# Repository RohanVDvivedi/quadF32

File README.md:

# Flight controller using STM32F103
[Documentation and demonstration video link](https://youtu.be/UyUF_jVTML4)

### setup requirements
(for programming stm32f103 microcontroller)

* Linux debian (to use make build system and code upload tool stm32flash)
* sublime/vi/vim/gedit any texteditor
* ARM cross compiler toolchain
  * sudo apt-get install gcc-arm-none-eabi binutils-arm-none-eabi
* stm32flash to flash the controller, assuming the controller has default factory bootloader
  * sudo apt-get install stm32flash
* stm32f103 microcontroller, with default factory bootloader (must)
* usb to uart converter
  * PL2303HX, CP2102, ftdi etc

### sensors
 * mpu6050  sccelerometer and gyroscope
 * hmc5883l magnetometer
 * ms5611 barometer

### additional accessories
 * rc transmitter and receiver

#### [STM32F10x Reference Manual](https://www.st.com/resource/en/reference_manual/cd00171190-stm32f101xx-stm32f102xx-stm32f103xx-stm32f105xx-and-stm32f107xx-advanced-arm-based-32-bit-mcus-stmicroelectronics.pdf)

### connections (from microcontroller)
 * I2c1 {PB6, PB7} -> GY86 sensor {SCL, SDA}
 * UART1 {PA10, PA9} -> UART debug port {RX, TX}
 * {PB10, PB11, PB12, PB13, PB14, PB15} -> RC receiver
 * {PA0, PA1, PA2, PA3} -> PWM to ESCs of corresponding motors (Left Front, Right Front, Left Back, Right Back) of Quadcopter
 
### PCB designs
 * You will find the .sch and .brd, QuadF32 flight controller board designs in the Eagle_CAD folder.
 * It would also include a generated .cam file that I used for building my board, I would request you to use a different cam file provided by your pcb manufacturer.
 * The folder also does include .lbr library for the stm32f103 module, that I am using.

### Third party acknowledgements
 * [STM32F103-c8t6 eagle cad library](https://os.mbed.com/users/hudakz/code/STM32F103C8T6_Hello/file/accb2c83a007/mbed-STM32F103C8T6.lib/)

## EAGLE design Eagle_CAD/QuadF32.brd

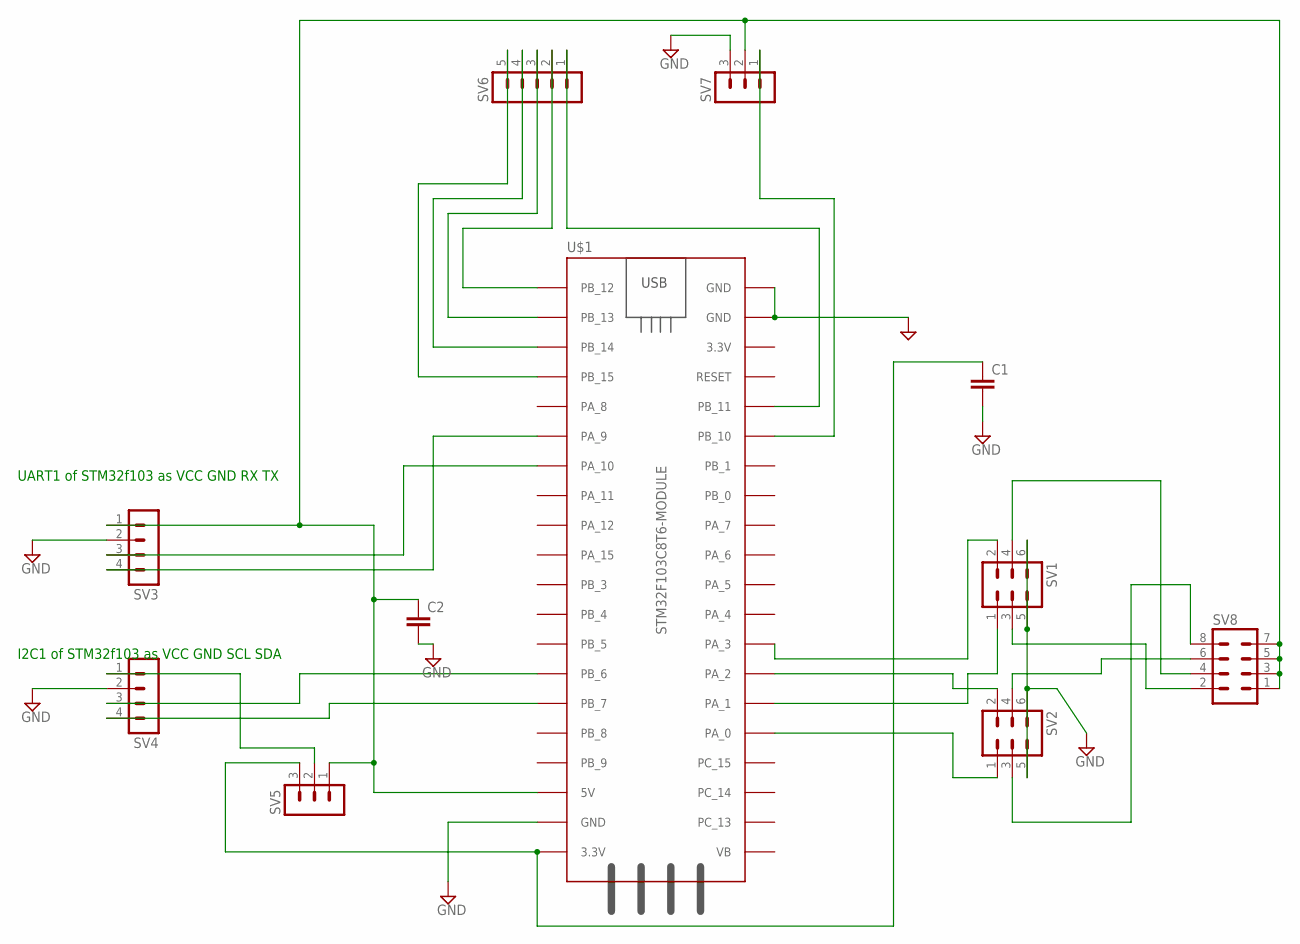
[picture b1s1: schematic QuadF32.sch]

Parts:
C1, C2: C5/2.5; C5B2.5
SV1, SV2: MA03-2
SV3, SV4: MA04-1
SV5, SV7: MA03-1
SV6: MA05-1
SV8: MA04-2
U$1: STM32F103C8T6-MODULE

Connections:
GND: C1.2, C2.2, SV1.5, SV1.6, SV2.5, SV2.6, SV3.2, SV4.2, SV7.3, U$1.GND_1 (GND), U$1.GND_2 (GND), U$1.GND_3 (GND)
unnamed: SV4.3, U$1.PB_6
unnamed: SV4.4, U$1.PB_7
unnamed: SV3.3, U$1.PA_10
unnamed: SV3.4, U$1.PA_9
unnamed: SV2.1, U$1.PA_0
unnamed: SV2.2, U$1.PA_2
unnamed: SV1.1, U$1.PA_1
unnamed: SV1.2, U$1.PA_3
unnamed: SV6.5, U$1.PB_15
unnamed: SV6.4, U$1.PB_14
unnamed: SV6.3, U$1.PB_13
unnamed: SV6.2, U$1.PB_12
unnamed: SV6.1, U$1.PB_11
unnamed: SV7.1, U$1.PB_10
unnamed: SV1.4, SV8.4
unnamed: C1.1, SV5.3, U$1.3.3V_1 (3.3V)
unnamed: SV4.1, SV5.2
unnamed: C2.1, SV3.1, SV5.1, SV7.2, SV8.1, SV8.3, SV8.5, SV8.7, U$1.5V
unnamed: SV2.3, SV8.8
unnamed: SV2.4, SV8.6
unnamed: SV1.3, SV8.2

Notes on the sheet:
UART1 of STM32f103 as VCC GND RX TX
I2C1 of STM32f103 as VCC GND SCL SDA

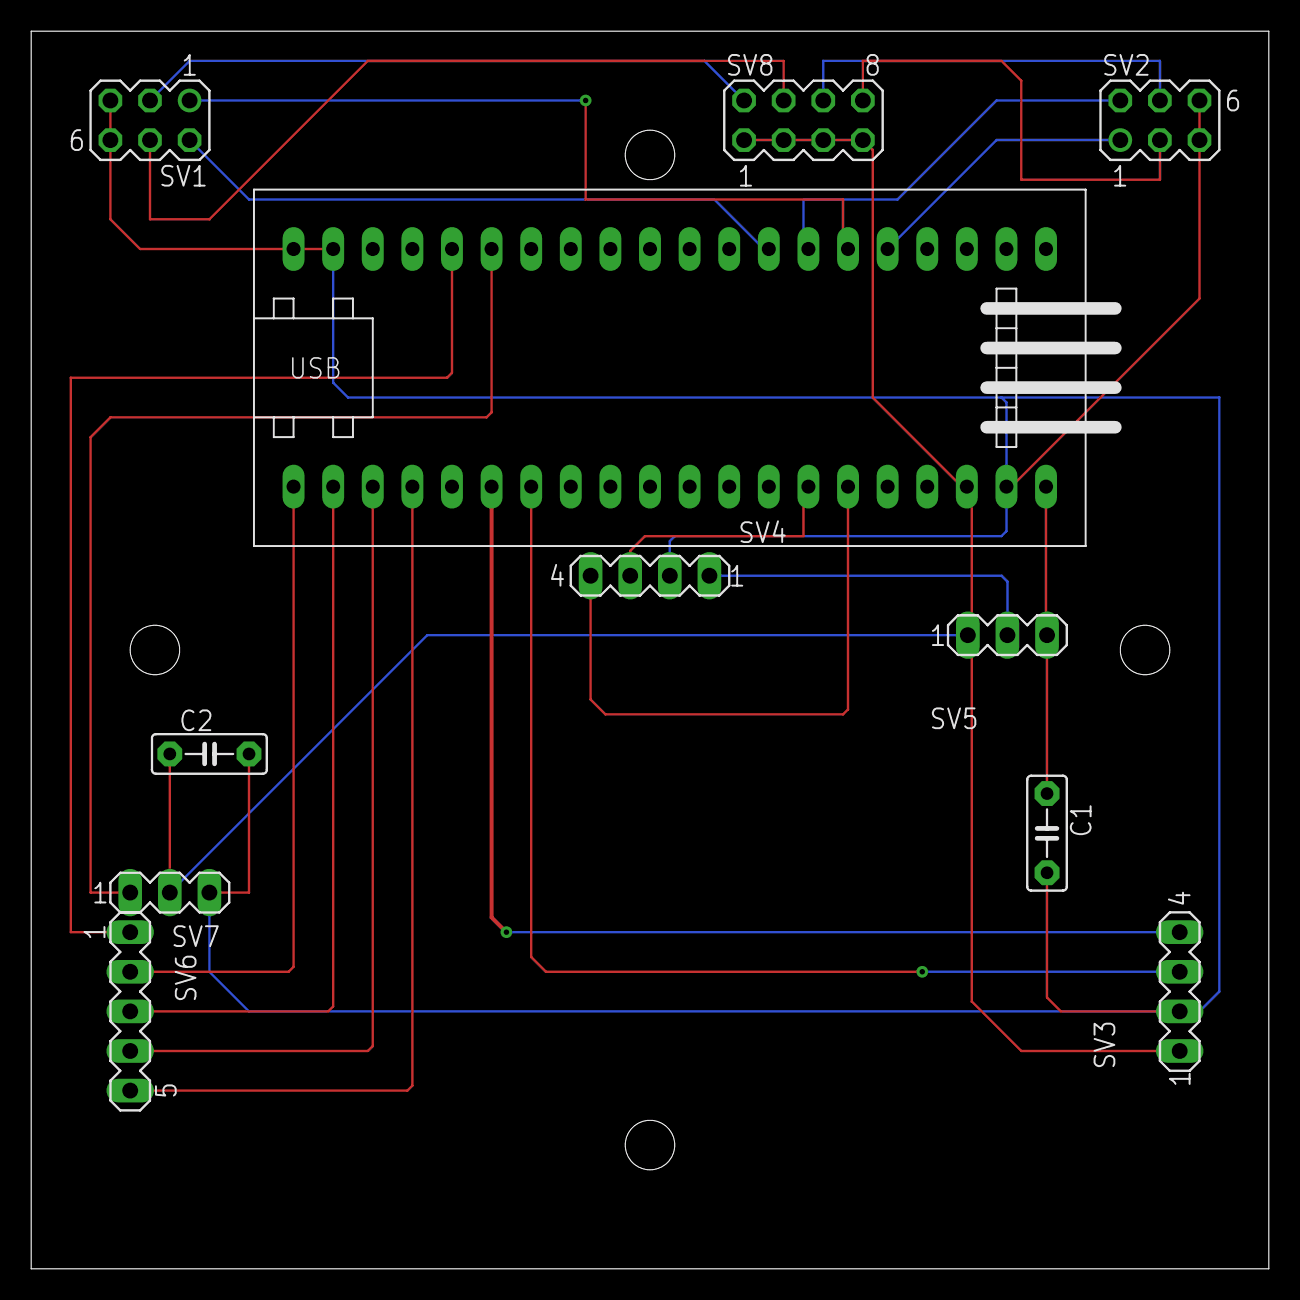
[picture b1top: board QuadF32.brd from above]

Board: 2 copper layers, 79.4 x 79.4 mm, 11 parts (0 on the bottom side), 22 nets.

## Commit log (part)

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2020-03-20 added all the files that would be required to be implementd for the project
2020-03-21 added sources for handling DMA got supporting i2c and usart
2020-03-21 building up the uart source, still in progress
2020-03-21 USART setup done - not working :(
2020-03-21 uart built but no success
2020-03-21 small bug corrected
2020-03-21 -- minor bug
2020-03-21 USART works and enough confidence to develop anything baremetal, made worlds worst mistake using macros for stuff for which structus are required
2020-03-22 added register definitions as structs
2020-03-22 project uses generic regsiter definitions from regs for USART
2020-03-22 using RCC registers from regs/usart only and uart initilized to use buadrate provided to it from uart_init parameters
2020-03-23 removed DMA header and source, we will only keep the source of DMA access separate and different to each requirement
2020-03-23 building separate definitions for dma and blocking access for uart writes
2020-03-23 DMA registers header and the test program setup
2020-03-23 only changed ordering of the registers setup in DMA
2020-03-23 Bare metal uart DMA working, DMA shows significant improvement on the CPU usage by offloading io on DMA great thing to learn by experience, next time, we hit delay functions in the nuts and instead u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
2020-03-23 added logic to handle clock source and frequency change
2020-03-23 working logic but the clock frequency of the processor is not chaging
2020-03-24 can cnahe from HSE to HSI, but not able to use PLL, flash and peripheral buses are setup accordingly, functions to get clock source or frequency setup correctly
2020-03-24 program reports its current clock frequency, no improvement still pll clock is not getting enabled
2020-03-24 something is working, but Do not know what, clock frequency has incressed, but the usart does not seem to work on that
2020-03-24 corrected the frequenccy finding logic and uart works
2020-03-24 started development for i2c, timers will be next
2020-03-25 implemented blocking function for i2c, not tested, I am sure they are going to be bugy
2020-03-25 few errors in implementation of i2c cleared
2020-03-25 built a small storage 8 bytes, a base line for funtioning of i2c tests
2020-03-25 few errors resolved, test program setup to handle i2c io
2020-03-26 a lot of debug code still litters in i2c i2c driver not built yet, need a lot of time to work
2020-03-26 i2c lines are getting driven by master stm32 bug win
2020-03-26 most issues resolved, driver io
2020-03-26 reads works flawlessly only 1 time :p
2020-03-26 best impl uptill now
2020-03-26 read and write all working cool, for atleast 1 byte, larger byte io and dma with i2c are next goals
2020-03-26 built completely functional test code for i2c driver, works flawlessly
2020-03-26 due to the nature of the program, we need blocking writes to uart, i2c device address can now be changed
2020-03-27 final nail in the i2c master driver of stm32, fully functional, for register address and data based sensors, plain format or command based protocols example the one used by barometer sensors need few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
2020-03-31 added timer registers that wil be used to drive bldc motors for the quadcopter
2020-03-31 started building logic for controlling bldc motors
2020-03-31 need to add registers and configuration rebuilding because we will have to use a similar timer 2, instead of timer 1
2020-04-01 since all the registers for all the timers are idnetically structures, we club all of them as just timers
2020-04-01 all timers under one roof
2020-04-01 added bldc function to main for testing
2020-04-01 added and trying to amke and test timer2 with bldc, but not working
2020-04-01 set everything up according to the requirements from the datasheet
2020-04-01 output compare now wors
2020-04-01 bldc motor module is working flawlessly
2020-04-03 added logic to use timer 3 for receiving data from rc channe;
2020-04-04 using traditional style interrupt based any pin rc receiver captre, istead t of my new idea of relying solely on timer input captures
2020-04-04 onlu interrupt attach part is remaining
2020-04-05 added external interrupt registers
2020-04-05 added logic to check if the given pin created the external interrupt, also a minor bug resolved
2020-04-05 using afio module to alter interrupt pins from port a to port b and interrupts enabled
2020-04-05 modified the startup stript to handle external irq
2020-04-05 nvic and rcreceiver interrupts enabled, but the stuff is not set properly
2020-04-05 corrected pointer arithmethic for calculating the offset to EXTI10-15 interrupts
2020-04-05 external interrupt pins pulled down
2020-04-05 rc receiver NVIC not working
2020-04-05 temporarily this works, by setting the isr directly in the startup code -> bad practice by bad boy
2020-04-05 TImer 5 that was being used for the rc_receiver is not working
2020-04-05 forgot stm32f103 has only 4 counters, and I was using TIM5 :P xD
2020-04-06 modularizing the rc_receiver code. bug -> it accepts only one channel as input from all 6 ones, i.e. outof 6 channels if 2,3,5 are connected it will only pick the lowest channel the 2nd one, need to 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
2020-04-06 minor improvement
2020-04-06 if we clear the EXTI pending register at the end it works, except for the 4th channel :p
2020-04-07 removing debug statements
2020-04-15 copied all the required logic from quadf for picking up sensor data
2020-04-17 added read and write i2c raw commands
2020-04-17 added necessary files to proceed with the rtc clock as the new micros clock, this will reduce the logic on various other modules also we would get a very precide delay
2020-04-17 rtc clock setup done
2020-04-17 added lod and new code both to test and work
2020-04-17 going by the rules of the datasheet we need to return and check the missing points that we skipped in over confidence :p
2020-04-17 rtc working as expected
2020-04-17 until time added to make certain logic easier to control and time
2020-04-17 minor change printing z axis valies since a good serializer logic is not avalable in the project
2020-04-18 added things that will help in debugging
2020-04-21 added pid logic
2020-04-21 added register definitions for the backup domain register, we will be using them for the backup domain
2020-04-21 there are only 10 backup data registers
2020-04-22 added backup registers
2020-04-23 minor bug resolved in stringify double
2020-04-23 built the very simple flight controller logic almost all the blocks are completed
2020-04-23 mapped and corrected rc input values
2020-04-23 added functionality to detect if the rc receiver is detected
2020-04-23 added protection against out of bound motor values
2020-04-28 added necessary tuning macros, for pid
2020-04-28 just testing motors initially
2020-04-30 made the flight controller completely tunable, removing all the unnecesary logic from the updating pid constants, clearing logic as required
2020-05-02 debug statements removed
2020-05-02 pid constants update no matter what
2020-05-02 error with motor directions
2020-05-02 changing the aux limits for PI gains, motor directiond for x and y axis are correct
2020-05-03 -- minor changes temporary
2020-05-03 need to give some time for the mpu6050 to start up before we start working with it
2020-05-03 removing redundant delay and setting aux2 to 0 to test the bug
2020-05-07 added macros to help calibrating ESCs on startup
2020-06-11 added insensitivity for min side of aux values
2020-06-11 setup completed
2020-06-13 test rig compliant values
2020-06-14 tested x axis with same values as y and tests passed
2020-06-15 added functionality for calculating absolute roll and pitch for the controller
2020-06-15 added -lm for math library
2020-06-15 al doubles converted to floats
2020-06-15 using simple precission float literals and float functions reducing executable size by about 1 kilobyte
2020-06-15 stable mode for roll and pitch axis
2020-06-15 formalzing constant to place them as macros
2020-06-15 trying to hand tune pids
2020-06-17 tuning x axis first
2020-06-17 x and y tuning values tested by hand and are quite close to 2.3, 0.0005
2020-06-18 pid intergral values are also clipped
2020-06-18 increasing the pid limits to get better coverng
2020-06-19 changing custom min max implementation to math library fminf and fmaxf library implementation
2020-06-19 bringing code to normal state
2020-06-20 3.5 is a pid controller saturation limit for the pid controller in the given testcase
2020-06-20 copter having relatively the most stable till date flight
2020-06-20 minor oscillations but the results are great
2020-06-20 slightly lower i gain but this is good enough
2020-06-20 remarkedly the best pid values uptill now
2020-06-20 very slow control over drone, reducing the p gain surely helped with overshooting motor
2020-06-20 using z required for rate control with the same pid values as pitch and roll axis
2020-06-20 converging to better
2020-06-20 baack to square 1, having the same pid tuning as the old copter
2020-06-21 testing with almost as good values
2020-06-21 Pitch and roll axis pid values tuned very well
2020-06-22 pid propotional z axis gain is now flyable on atleast the indoor test bench
2020-06-22 defining throttle min and max values to be written when pid is activated or not
2020-06-22 ridding of redundant typecasts
2020-06-23 stable flight looks promising on outdoors
2020-06-23 incresing sensitivilty tto controll by redung insensitivity limits in x, y axis
2020-06-23 limits for the imput rc receviver channel values have been limitted by global macros
2020-06-23 increased I gain shows higher stability and teadiness in the inner faster loop, reducing outer slow pid p gain to reduce oscillations
2020-06-23 restructuring for simplified versioning
2020-06-23 there can not be better rate pid values
2020-06-23 rate pid made softer to accomodate room for variations given by angle controller
2020-06-23 yaw pid tuned and snce the values have been almost double, of the rate pid of pitch and roll axis, they have also been made the same
2020-06-23 renaming to make way for futher pids
2020-06-24 reducing p and d gains to get rid of oscillations completely, but the response has become smooth now
2020-06-24 stacking to the rate controller for now
2020-06-24 using slowly stabilize as required mode
2020-06-24 successfull maiden flight using only the rate controller
2020-06-24 setup for further steps in angle controller tuning
2020-07-17 make file upgraded, starup code fixated to use main as the _start function
2020-07-17 missing flags architecture flags
2020-08-28 added eagle cad files for board to the project
2020-08-28 added readme details to eagle cad pcb files
2020-10-05 changing constants for pid tuning
2020-10-07 final PID angular rate control units
2020-10-15 final rate controller tuning completed
2020-10-18 minor changes using a managable I gain with high P gain for better response time
2020-10-27 yaw control just can not be better - alttitude controll is the next
2020-10-28 none change- ESC issues so need higher D gain on attitude rate
2020-10-28 added future tasks for the quadf32 project
2020-10-29 with higher D gain its easier to set higher p gain- higher p gain means higher responsive ness
2020-10-30 lowered I gain gives less robotic feel
2020-10-30 good enough gains for maneuvering, but oscillates
2020-10-30 need to debug rc receiver errors in values recevived on controller reset
2020-10-31 lowered d-gain, but very small oscillations, little lesser i gain is still working, yet very fast maneuvering is not possible yet
2020-11-01 better faster yaw control, smoother and faster attitude, -> oscillations disappear, still P gain feels lighter on attitude and can be increased -> finally it would be better to add angle stab control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
2020-11-06 updated tuning constants PD or rate gain, to allow higher P with a bit more oscillations and altitude gain, this enables for a better angle controller tuning
2020-11-08 updated gains after retuning rate gains mainly reducing d gains for stab gains issue
2021-03-26 geting rid of redundant transformations on the gyrodata
2021-03-27 started dev for attitude angle controller
2021-03-27 need extra braces arround macro params
2021-03-27 using initializaion abs roll and pitch values to fix the fixed initial attitude
2021-03-27 fix in using macro for STAB PID
